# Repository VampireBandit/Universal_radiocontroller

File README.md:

# Transceiver_101
This is a universal remote controller for almost any remote device e.g. Planes,drones,boats or rc cars. It can be mounted and set up in any custom project the needs remote controlling.
---

# Key Features 
-can be used to controll almost any project

-customisable for drone flight controllers

-6 channel controller

-up to 2.5km range 

-2 customizable toggle switch

-Custom code to change as needed

# Images

There is a notch that shuold be kept in mind. 

# BOM

| Name | Purpose | Quantity |
| :--- | :--- | :--- |
| **Toggle switch** | Master power | 1 |
| **PCB** | Circuit board | 2 |
| **Enclosure** | The casing | 1 |
| **Battery** | Power | 2 |
| **Male headers** | Connection | 8 |
| **Female Headers** | Mounting | 56 |
| **100nf capacitor** | Voltage capping | 4 |
| **10uf capacitor** | Voltage regulation | 2 |
| **100uf capacitor** | Voltage regulation | 2 |
| **Arduino Nano** | MCU | 2 |
| **Antenna** | Receiver antenna | 1 |
| **Receiver Module** | Radio transmission | 1 |
| **LM1117T-3.3** | Voltage regulator | 2 |
| **Toggle switch** | Channel switch | 2 |
| **PS4 Analog** | Controlling | 2 |

# Firmware
This remote and receiver uses C++ that is for arduino IDE

Made by Rubaiyat Islam

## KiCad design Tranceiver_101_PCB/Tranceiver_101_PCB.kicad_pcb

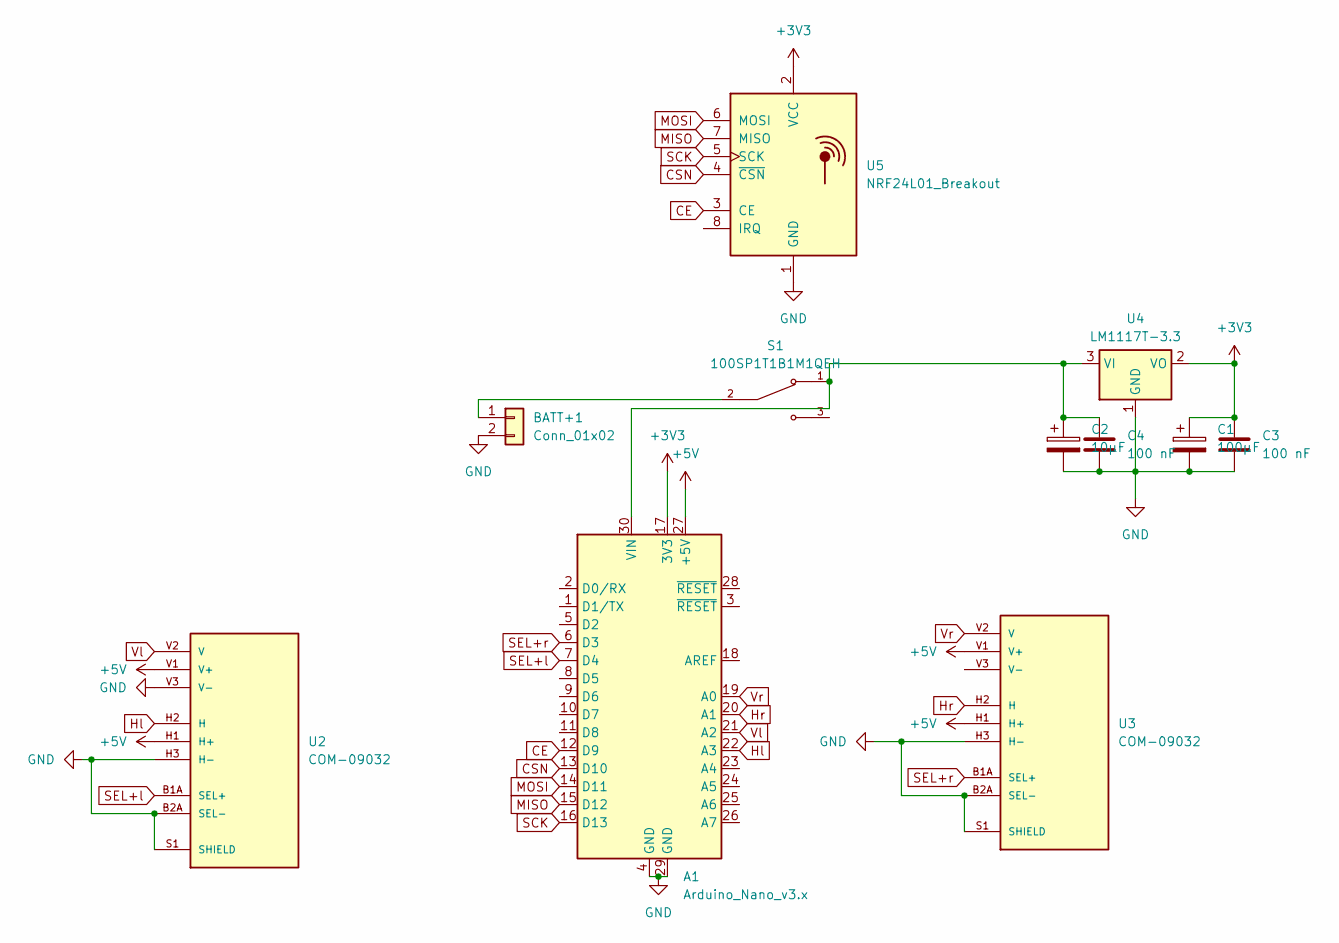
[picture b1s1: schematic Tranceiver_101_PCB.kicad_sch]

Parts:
A1: Arduino_Nano_v3.x; Arduino_Nano
BATT+1: Conn_01x02; PinHeader_1x02_P2.54mm_Vertical
C1: 100µF; CP_Radial_D8.0mm_P3.50mm
C2: 10µF; CP_Radial_D5.0mm_P2.00mm
C3, C4: 100 nF; C_Disc_D5.0mm_W2.5mm_P2.50mm
S1: 100SP1T1B1M1QEH; SW_100SP1T1B1M1QEH; PARTREV D
U2, U3: COM-09032; XDCR_COM-09032; PARTREV N/A
U4: LM1117T-3.3; TO-220-3_Horizontal_TabDown
U5: NRF24L01_Breakout; nRF24L01_Breakout

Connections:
+3V3: A1.17 (3V3), C1.1, C3.1, U4.2 (VO), U5.2 (VCC)
+5V: A1.27 (+5V), U2.H1 (H+), U2.V1 (V+), U3.H1 (H+), U3.V1 (V+)
CE: A1.12 (D9), U5.3 (CE)
CSN: A1.13 (D10), U5.4 (~CSN)
GND: A1.4 (GND), A1.29 (GND), BATT+1.2, C1.2, C2.2, C3.2, C4.2, U2.B2A (SEL-), U2.H3 (H-), U2.S1 (SHIELD), U2.S2 (SHIELD), U2.S3 (SHIELD), U2.S4 (SHIELD), U2.V3 (V-), U3.B2A (SEL-), U3.H3 (H-), U3.S1 (SHIELD), U3.S2 (SHIELD), U3.S3 (SHIELD), U3.S4 (SHIELD), U4.1 (GND), U5.1 (GND)
Hl: A1.22 (A3), U2.H2 (H)
Hr: A1.20 (A1), U3.H2 (H)
MISO: A1.15 (D12), U5.7 (MISO)
MOSI: A1.14 (D11), U5.6 (MOSI)
unnamed: A1.30 (VIN), C2.1, C4.1, S1.1, U4.3 (VI)
unnamed: BATT+1.1, S1.2
SCK: A1.16 (D13), U5.5 (SCK)
SEL+l: A1.7 (D4), U2.B1A (SEL+)
SEL+r: A1.6 (D3), U3.B1A (SEL+)
Vl: A1.21 (A2), U2.V2 (V)
Vr: A1.19 (A0), U3.V2 (V)

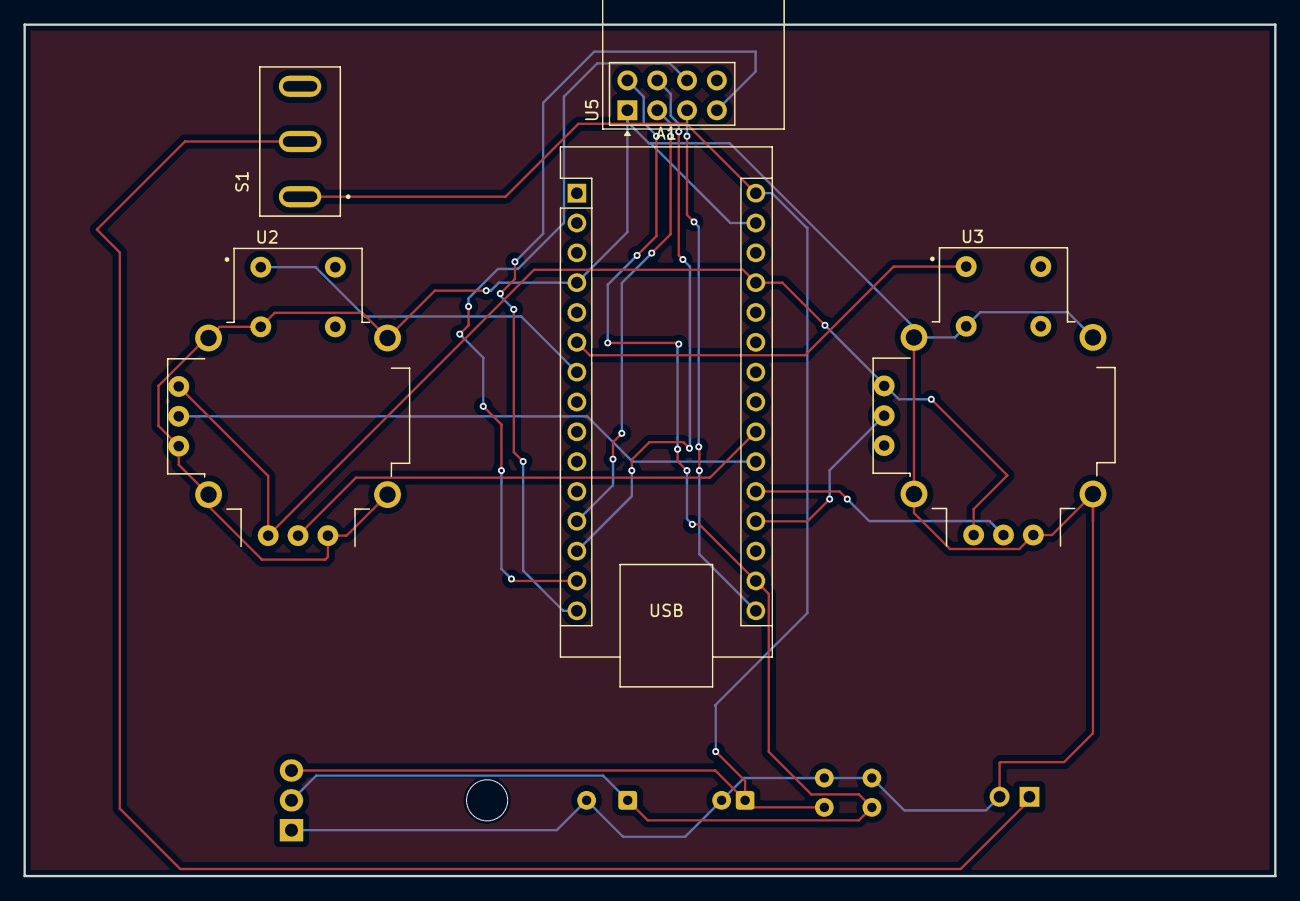
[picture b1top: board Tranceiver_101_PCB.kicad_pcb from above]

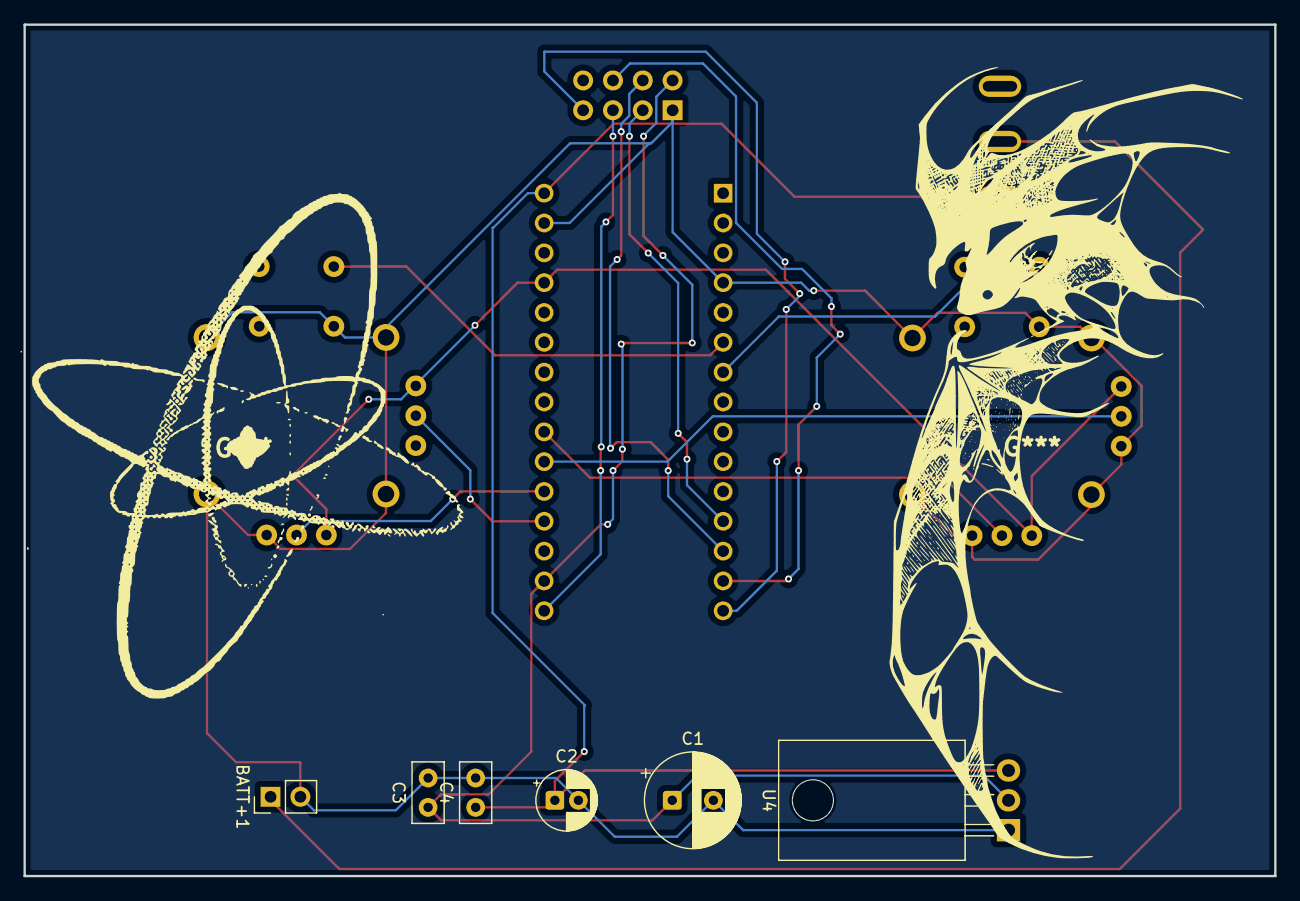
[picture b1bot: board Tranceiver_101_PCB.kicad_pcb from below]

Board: 2 copper layers, 106.5 x 72.5 mm, 11 parts (6 on the bottom side), 16 nets.

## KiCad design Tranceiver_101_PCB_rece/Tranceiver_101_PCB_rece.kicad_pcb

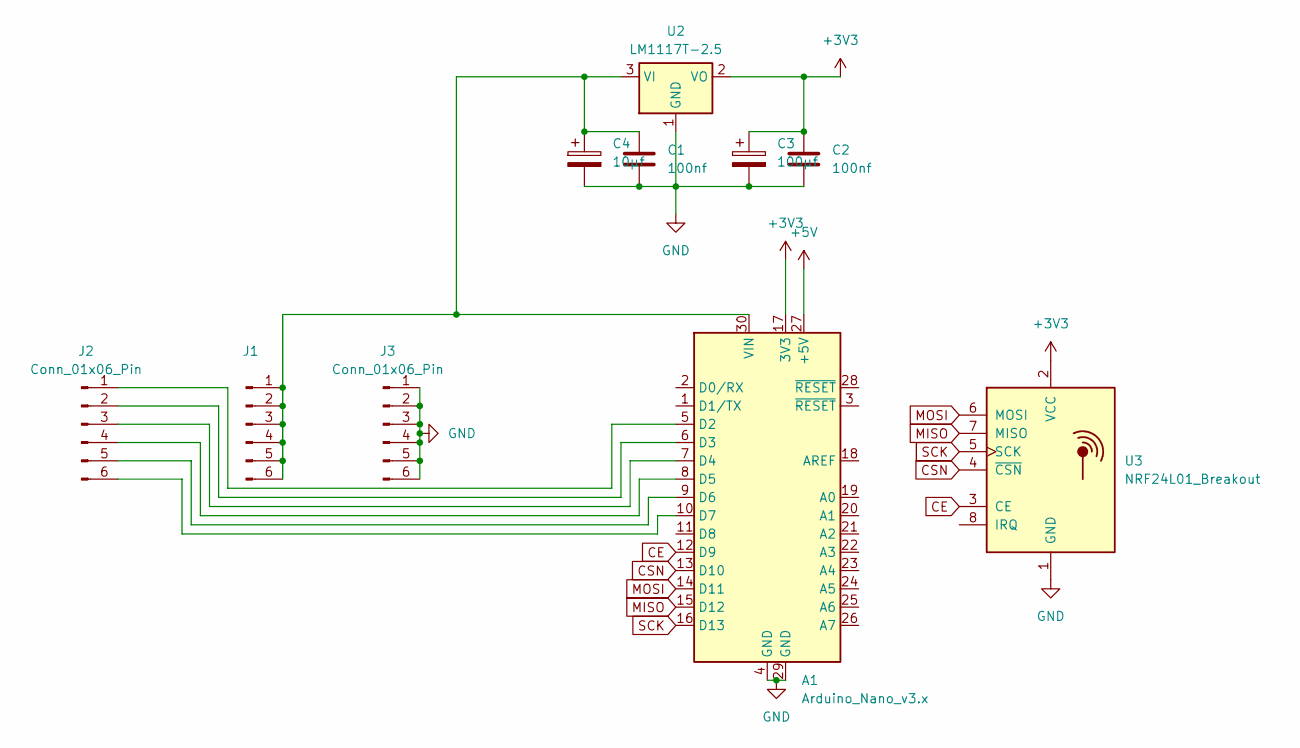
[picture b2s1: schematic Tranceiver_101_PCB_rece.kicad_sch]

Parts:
A1: Arduino_Nano_v3.x; Arduino_Nano
C1, C2: 100nf; C_Disc_D5.0mm_W2.5mm_P2.50mm
C3: 100μf; CP_Radial_D8.0mm_P3.50mm
C4: 10μf; CP_Radial_D5.0mm_P2.00mm
J1, J2, J3: Conn_01x06_Pin; PinHeader_1x06_P2.54mm_Vertical
U2: LM1117T-2.5; TO-220-3_Horizontal_TabDown
U3: NRF24L01_Breakout; nRF24L01_Breakout

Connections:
+3V3: A1.17 (3V3), C2.1, C3.1, U2.2 (VO), U3.2 (VCC)
+5V: A1.27 (+5V)
CE: A1.12 (D9), U3.3 (CE)
CSN: A1.13 (D10), U3.4 (~CSN)
GND: A1.4 (GND), A1.29 (GND), C1.2, C2.2, C3.2, C4.2, J3.1, J3.2, J3.3, J3.4, J3.5, J3.6, U2.1 (GND), U3.1 (GND)
MISO: A1.15 (D12), U3.7 (MISO)
MOSI: A1.14 (D11), U3.6 (MOSI)
unnamed: A1.5 (D2), J2.1
unnamed: A1.6 (D3), J2.2
unnamed: A1.7 (D4), J2.3
unnamed: A1.8 (D5), J2.4
unnamed: A1.9 (D6), J2.5
unnamed: A1.10 (D7), J2.6
unnamed: A1.30 (VIN), C1.1, C4.1, J1.1, J1.2, J1.3, J1.4, J1.5, J1.6, U2.3 (VI)
SCK: A1.16 (D13), U3.5 (SCK)

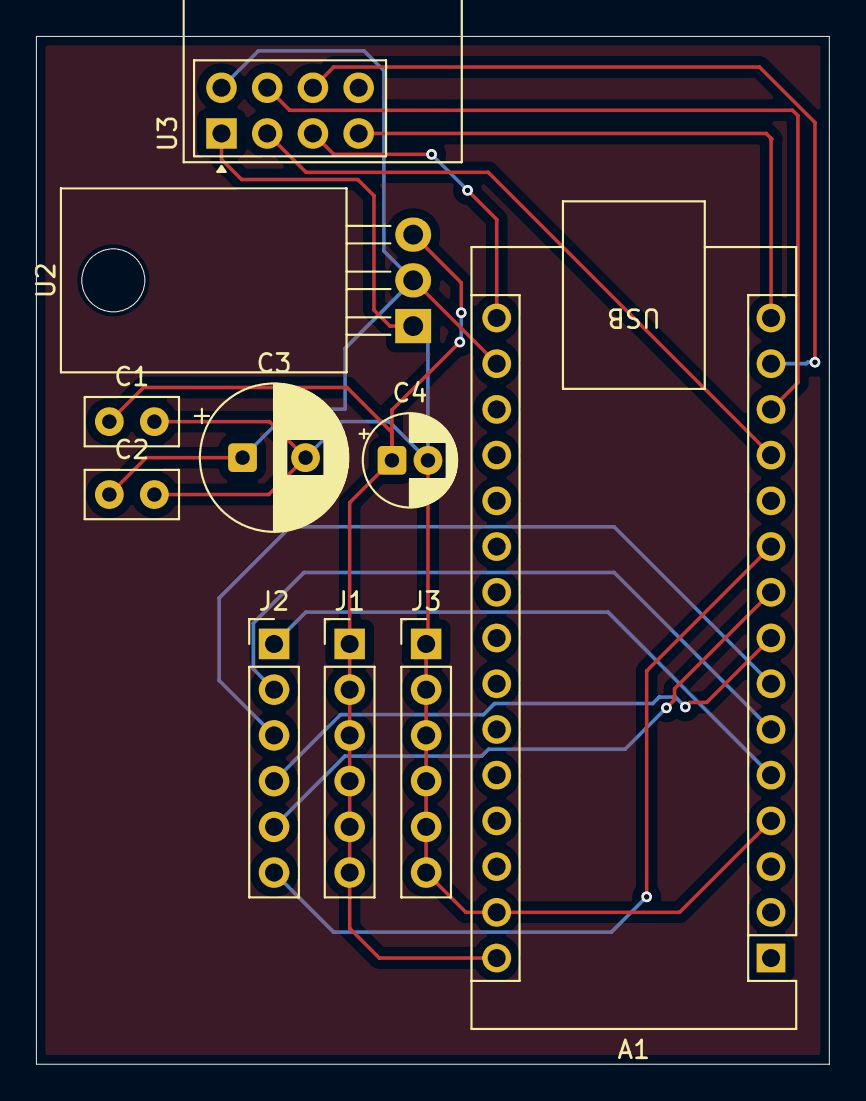
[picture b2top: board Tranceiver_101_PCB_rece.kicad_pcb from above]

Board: 2 copper layers, 44.1 x 57.1 mm, 10 parts (0 on the bottom side), 14 nets.

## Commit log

2026-03-11 Needed to add switch
2026-03-11 Added a line to fit jlc
2026-04-02 Some More pics for proper view
2026-04-02 Added Pics
2026-04-10 Revise BOM section in README.md
    Updated parts list for the project and removed redundant items.
